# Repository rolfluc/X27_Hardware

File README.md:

# X27_Hardware
Repo to house the Hardware file for the x27 Dial Motor

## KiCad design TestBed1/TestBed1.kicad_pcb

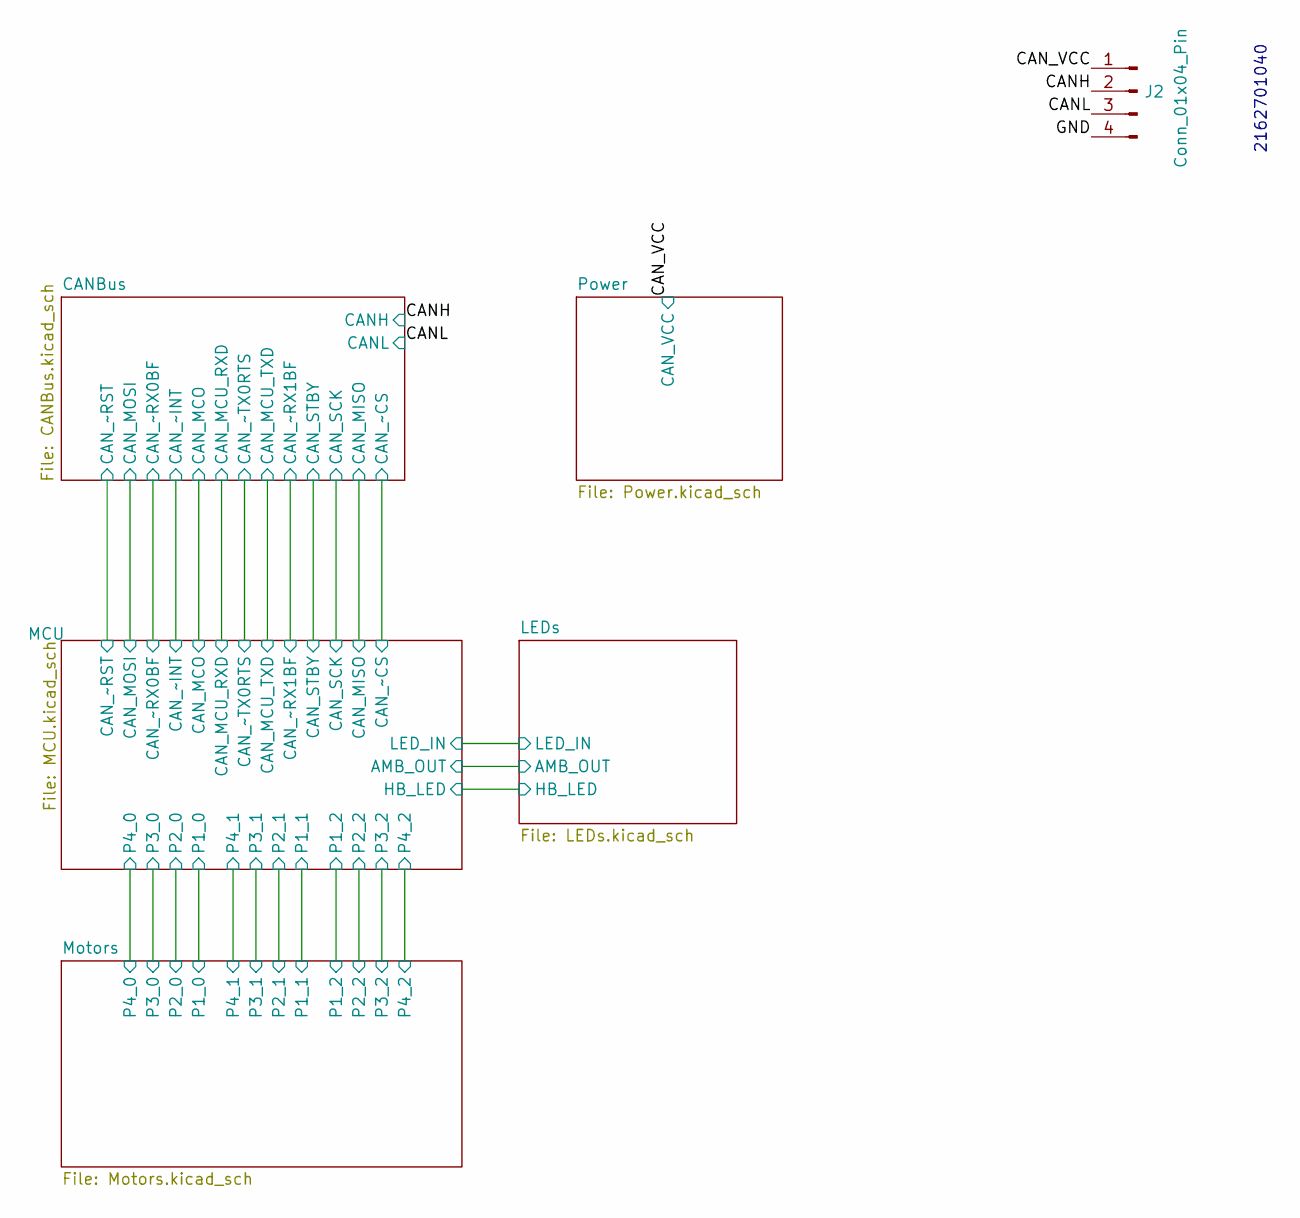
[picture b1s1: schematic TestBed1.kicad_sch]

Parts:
J2: Conn_01x04_Pin; CONN_70551-xxxx_04_MOL

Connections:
/CANH: J2.2; also elsewhere on the board
/CANL: J2.3; also elsewhere on the board
/CAN_VCC: J2.1; also elsewhere on the board
/GND: J2.4

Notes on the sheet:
2162701040

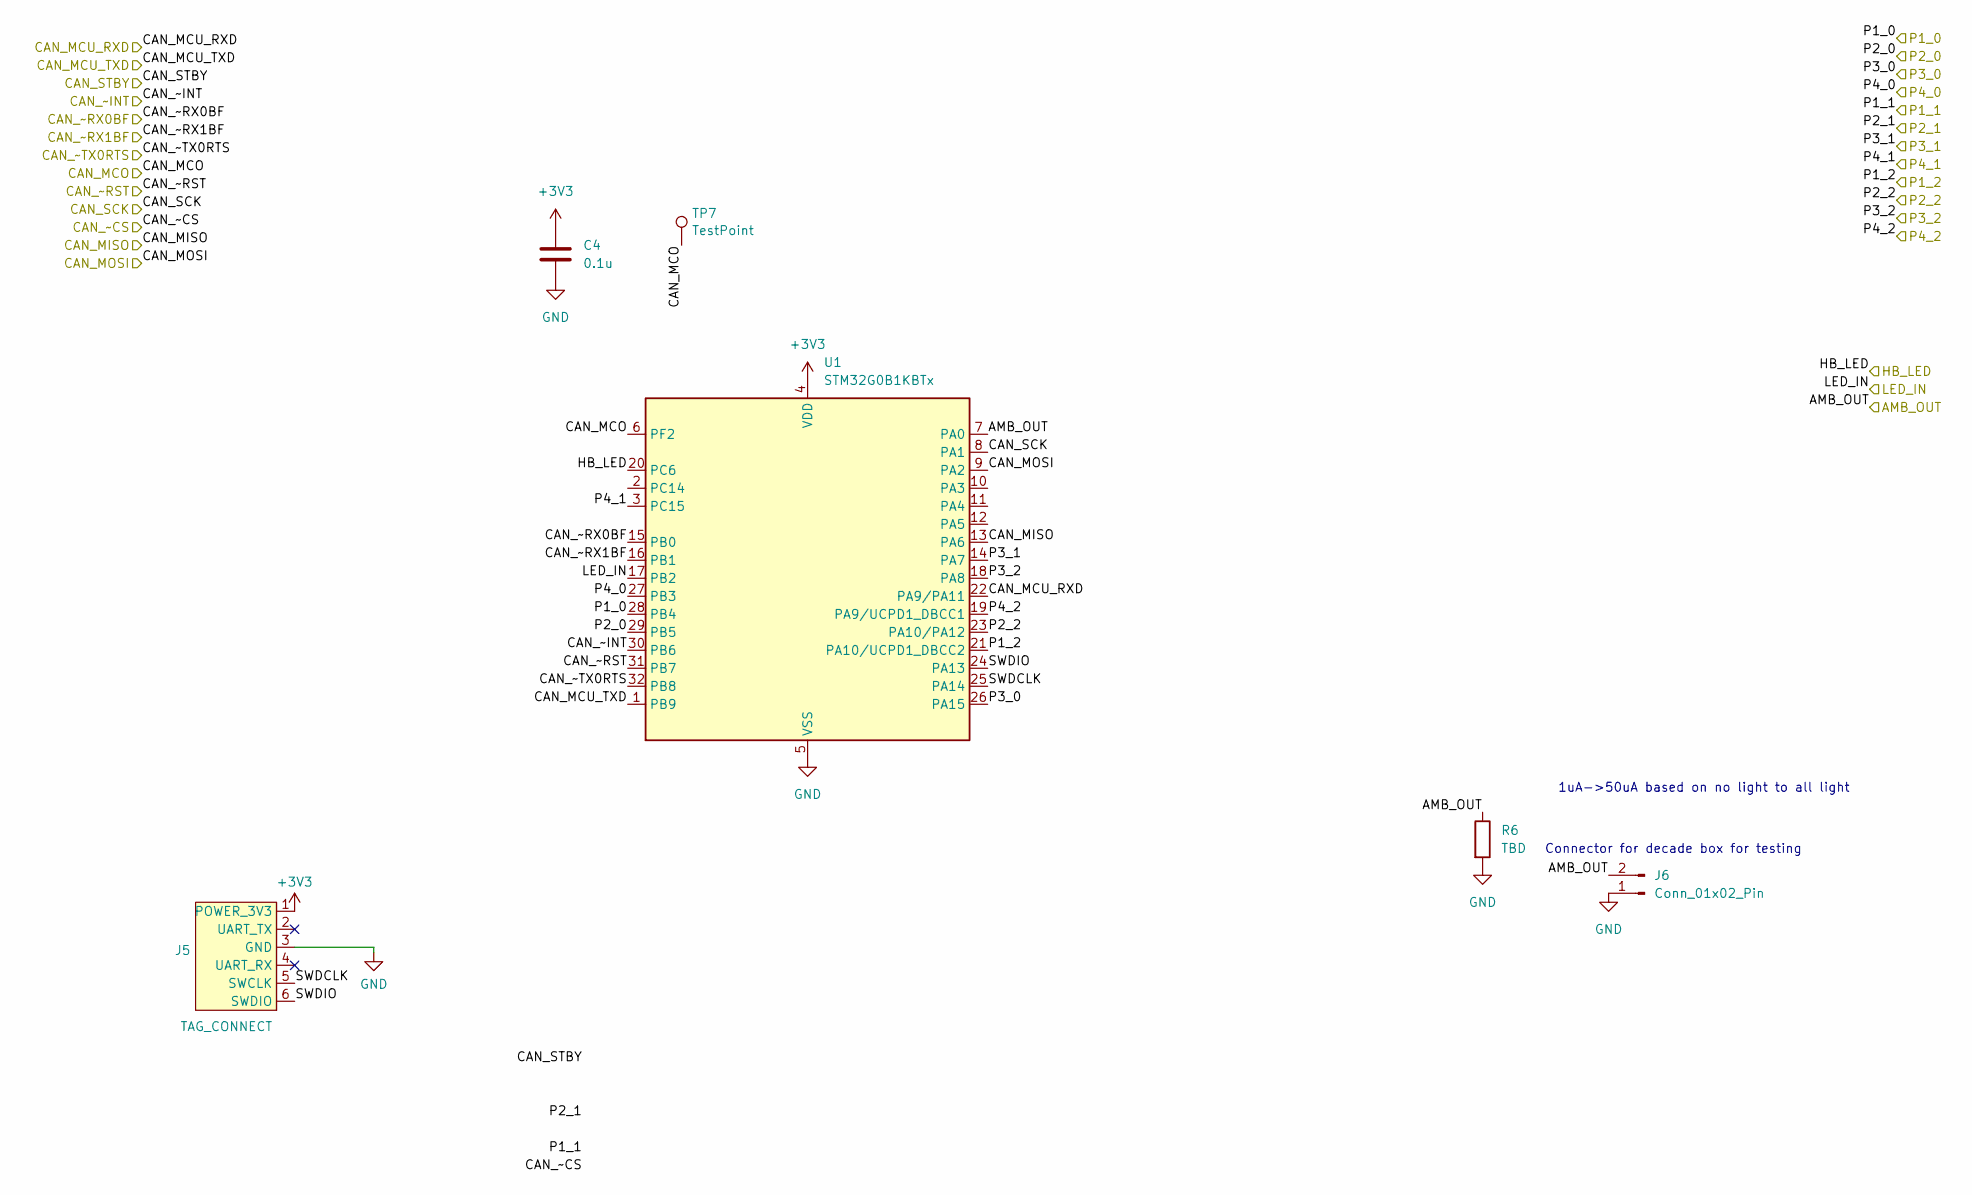
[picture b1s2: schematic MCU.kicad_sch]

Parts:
C4: 0.1u; C_0402_1005Metric_Pad0.74x0.62mm_HandSolder
J5: TAG_CONNECT; Tag-Connect_TC2030-IDC-FP_2x03_P1.27mm_Vertical
J6: Conn_01x02_Pin; PinHeader_1x02_P1.27mm_Vertical
R6: TBD; R_0402_1005Metric
TP7: TestPoint; TestPoint_Pad_1.0x1.0mm
U1: STM32G0B1KBTx; LQFP-32_7x7mm_P0.8mm

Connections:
+3V3: C4.1, J5.1 (POWER_3V3), U1.4 (VDD); also elsewhere on the board
/CANBus/CAN_MCO: TP7.1, U1.6 (PF2); also elsewhere on the board
/CANBus/CAN_MCU_RXD: U1.22 (PA9/PA11); also elsewhere on the board
/CANBus/CAN_MCU_TXD: U1.1 (PB9); also elsewhere on the board
/CANBus/CAN_MISO: U1.13 (PA6); also elsewhere on the board
/CANBus/CAN_MOSI: U1.9 (PA2); also elsewhere on the board
/CANBus/CAN_SCK: U1.8 (PA1); also elsewhere on the board
/CANBus/CAN_~INT: U1.30 (PB6); also elsewhere on the board
/CANBus/CAN_~RST: U1.31 (PB7); also elsewhere on the board
/CANBus/CAN_~RX0BF: U1.15 (PB0); also elsewhere on the board
/CANBus/CAN_~RX1BF: U1.16 (PB1); also elsewhere on the board
/CANBus/CAN_~TX0RTS: U1.32 (PB8); also elsewhere on the board
/LEDs/AMB_OUT: J6.2, R6.1, U1.7 (PA0); also elsewhere on the board
/LEDs/HB_LED: U1.20 (PC6); also elsewhere on the board
/LEDs/LED_IN: U1.17 (PB2); also elsewhere on the board
/MCU/P1_0: U1.28 (PB4); also elsewhere on the board
/MCU/P1_2: U1.21 (PA10/UCPD1_DBCC2); also elsewhere on the board
/MCU/P2_0: U1.29 (PB5); also elsewhere on the board
/MCU/P2_2: U1.23 (PA10/PA12); also elsewhere on the board
/MCU/P3_0: U1.26 (PA15); also elsewhere on the board
/MCU/P3_1: U1.14 (PA7); also elsewhere on the board
/MCU/P3_2: U1.18 (PA8); also elsewhere on the board
/MCU/P4_0: U1.27 (PB3); also elsewhere on the board
/MCU/P4_1: U1.3 (PC15); also elsewhere on the board
/MCU/P4_2: U1.19 (PA9/UCPD1_DBCC1); also elsewhere on the board
/MCU/SWDCLK: J5.5 (SWCLK), U1.25 (PA14)
/MCU/SWDIO: J5.6 (SWDIO), U1.24 (PA13)
GND: C4.2, J5.3 (GND), J6.1, R6.2, U1.5 (VSS); also elsewhere on the board

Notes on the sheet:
1uA->50uA based on no light to all light
Connector for decade box for testing

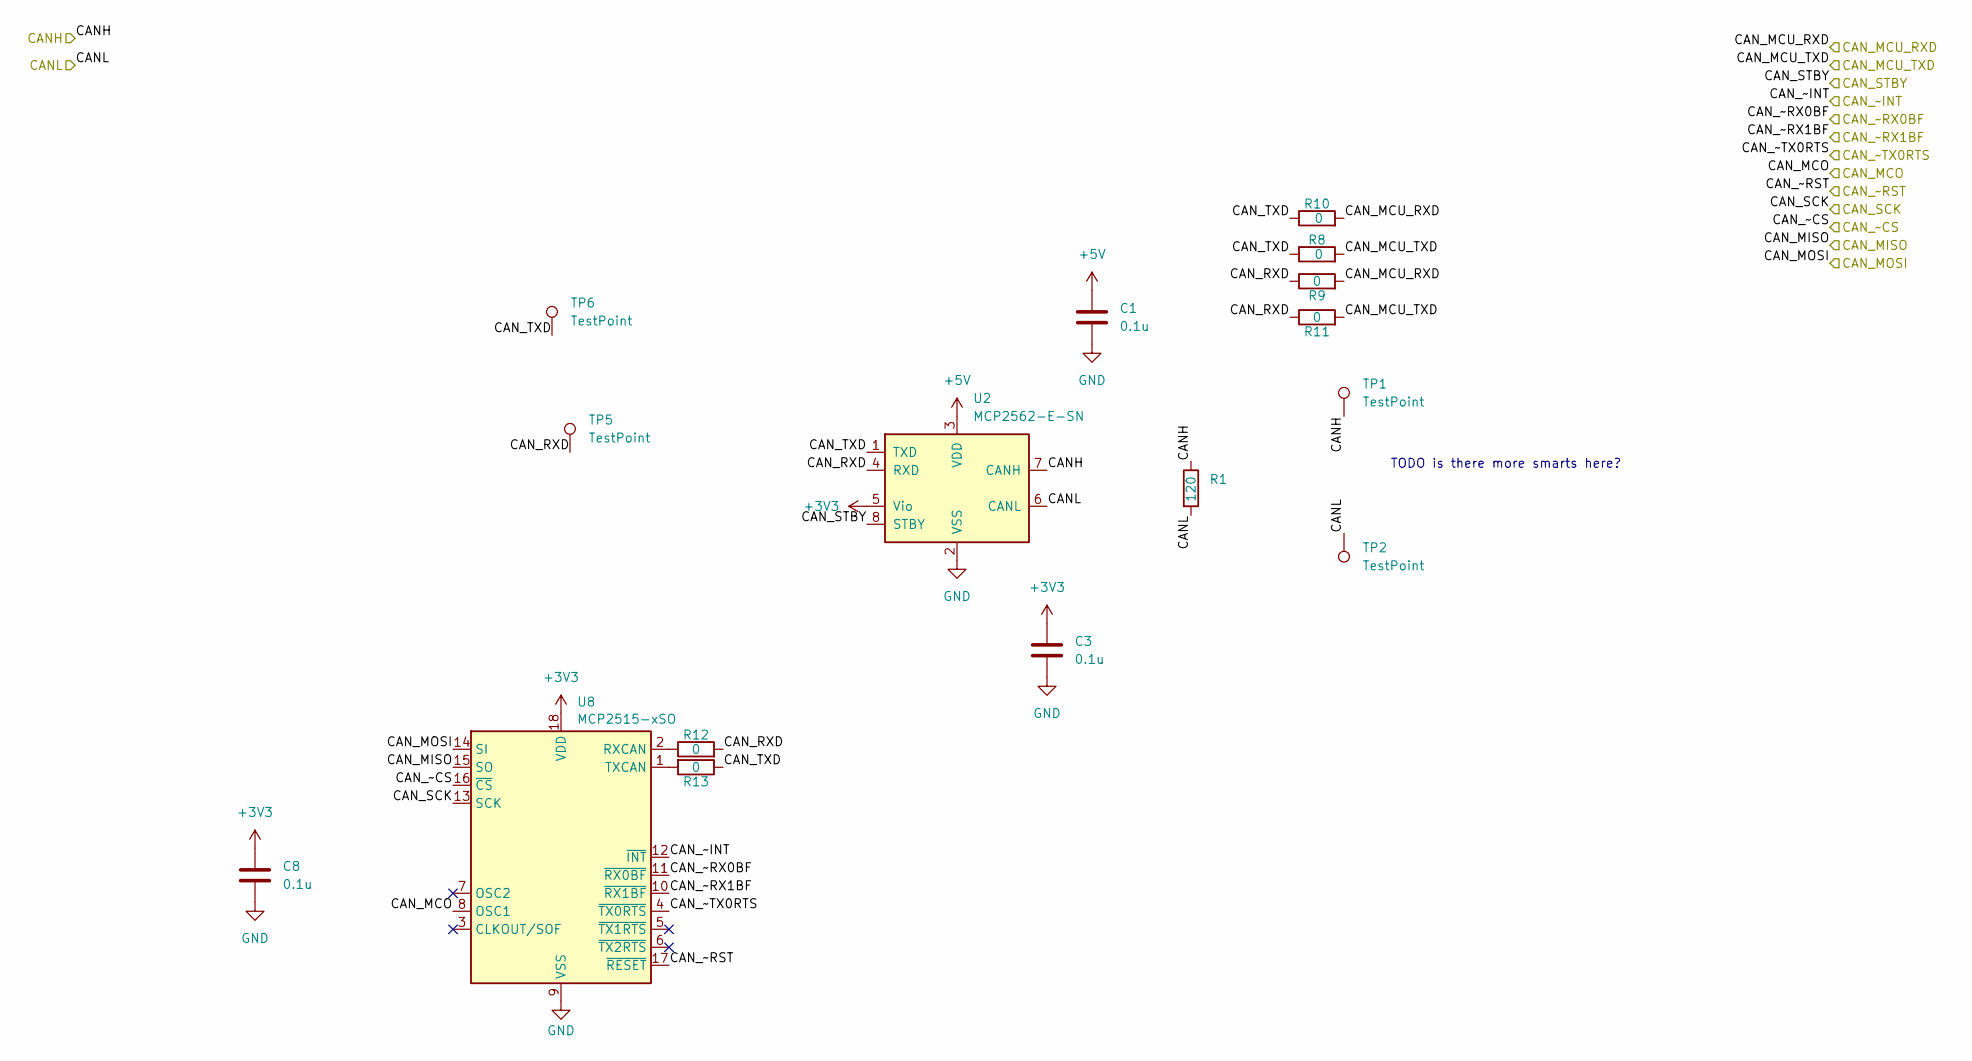
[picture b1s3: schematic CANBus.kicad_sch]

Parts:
C1, C3, C8: 0.1u; C_0402_1005Metric_Pad0.74x0.62mm_HandSolder
R1: 120; R_0805_2012Metric
R8, R9, R10, R11, R12, R13: 0; R_0402_1005Metric
TP1, TP2, TP5, TP6: TestPoint; TestPoint_Pad_1.0x1.0mm
U2: MCP2562-E-SN; SOIC-8_3.9x4.9mm_P1.27mm
U8: MCP2515-xSO; SOIC-18W_7.5x11.6mm_P1.27mm

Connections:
+3V3: C3.1, C8.1, U2.5 (Vio), U8.18 (VDD); also elsewhere on the board
+5V: C1.1, U2.3 (VDD); also elsewhere on the board
/CANBus/CAN_MCO: U8.8 (OSC1); also elsewhere on the board
/CANBus/CAN_MCU_RXD: R9.2, R10.2; also elsewhere on the board
/CANBus/CAN_MCU_TXD: R8.2, R11.2; also elsewhere on the board
/CANBus/CAN_MISO: U8.15 (SO); also elsewhere on the board
/CANBus/CAN_MOSI: U8.14 (SI); also elsewhere on the board
/CANBus/CAN_RXD: R9.1, R11.1, R12.2, TP5.1, U2.4 (RXD)
/CANBus/CAN_SCK: U8.13 (SCK); also elsewhere on the board
/CANBus/CAN_STBY: U2.8 (STBY)
/CANBus/CAN_TXD: R8.1, R10.1, R13.1, TP6.1, U2.1 (TXD)
/CANBus/CAN_~CS: U8.16 (~CS)
/CANBus/CAN_~INT: U8.12 (~INT); also elsewhere on the board
/CANBus/CAN_~RST: U8.17 (~RESET); also elsewhere on the board
/CANBus/CAN_~RX0BF: U8.11 (~RX0BF); also elsewhere on the board
/CANBus/CAN_~RX1BF: U8.10 (~RX1BF); also elsewhere on the board
/CANBus/CAN_~TX0RTS: U8.4 (~TX0RTS); also elsewhere on the board
/CANH: R1.1, TP1.1, U2.7 (CANH); also elsewhere on the board
/CANL: R1.2, TP2.1, U2.6 (CANL); also elsewhere on the board
GND: C1.2, C3.2, C8.2, U2.2 (VSS), U8.9 (VSS); also elsewhere on the board
unnamed: R12.1, U8.2 (RXCAN)
unnamed: R13.2, U8.1 (TXCAN)

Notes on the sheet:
TODO is there more smarts here?

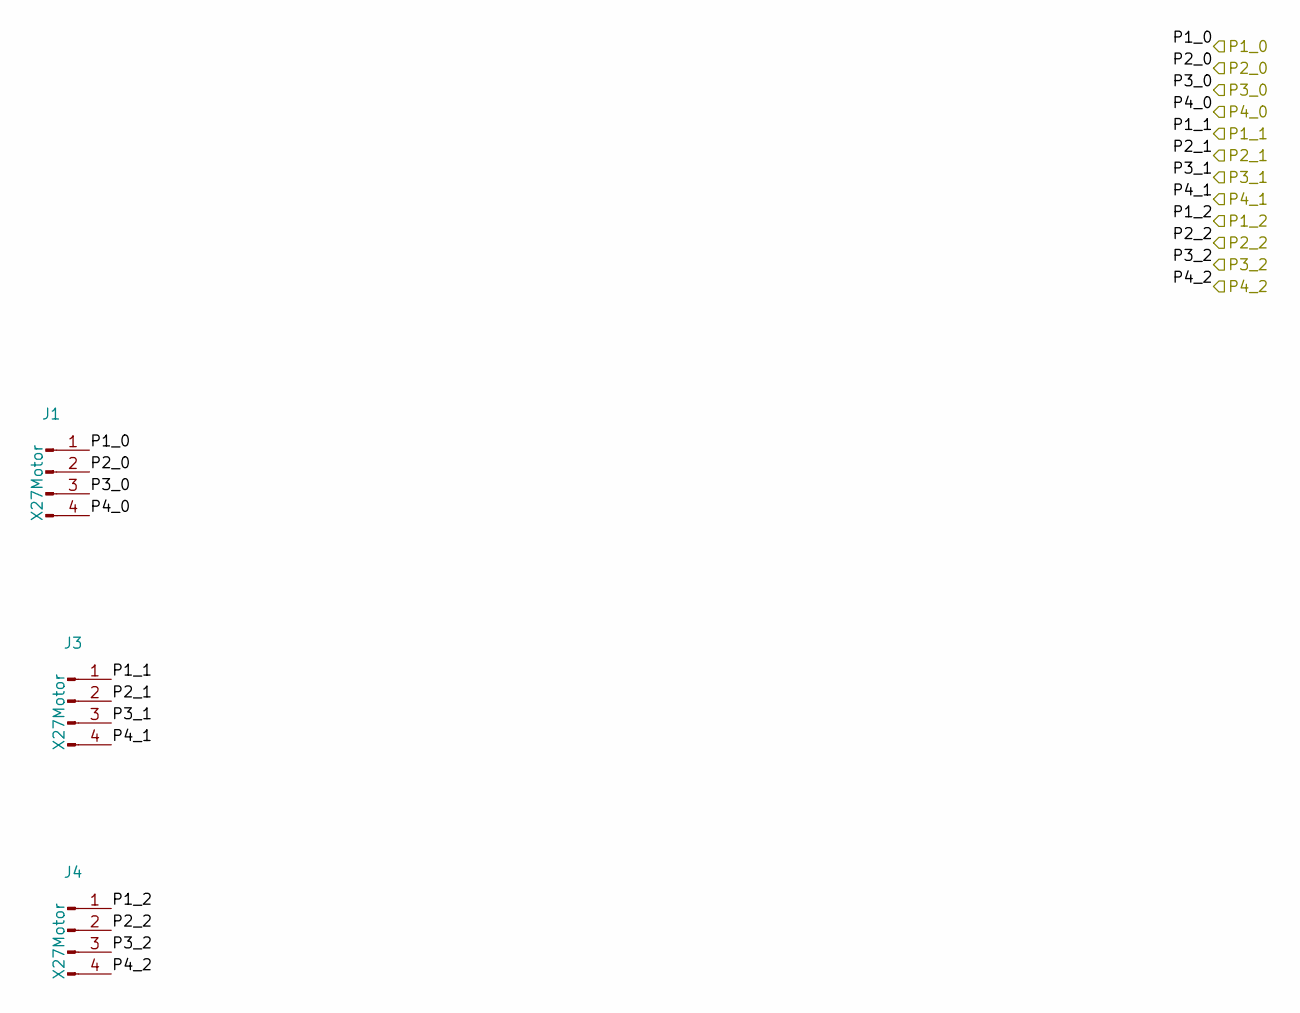
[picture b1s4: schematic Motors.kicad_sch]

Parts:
J1, J3, J4: X27Motor; X27-168

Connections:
/MCU/P1_0: J1.1; also elsewhere on the board
/MCU/P1_1: J3.1
/MCU/P1_2: J4.1; also elsewhere on the board
/MCU/P2_0: J1.2; also elsewhere on the board
/MCU/P2_1: J3.2
/MCU/P2_2: J4.2; also elsewhere on the board
/MCU/P3_0: J1.3; also elsewhere on the board
/MCU/P3_1: J3.3; also elsewhere on the board
/MCU/P3_2: J4.3; also elsewhere on the board
/MCU/P4_0: J1.4; also elsewhere on the board
/MCU/P4_1: J3.4; also elsewhere on the board
/MCU/P4_2: J4.4; also elsewhere on the board

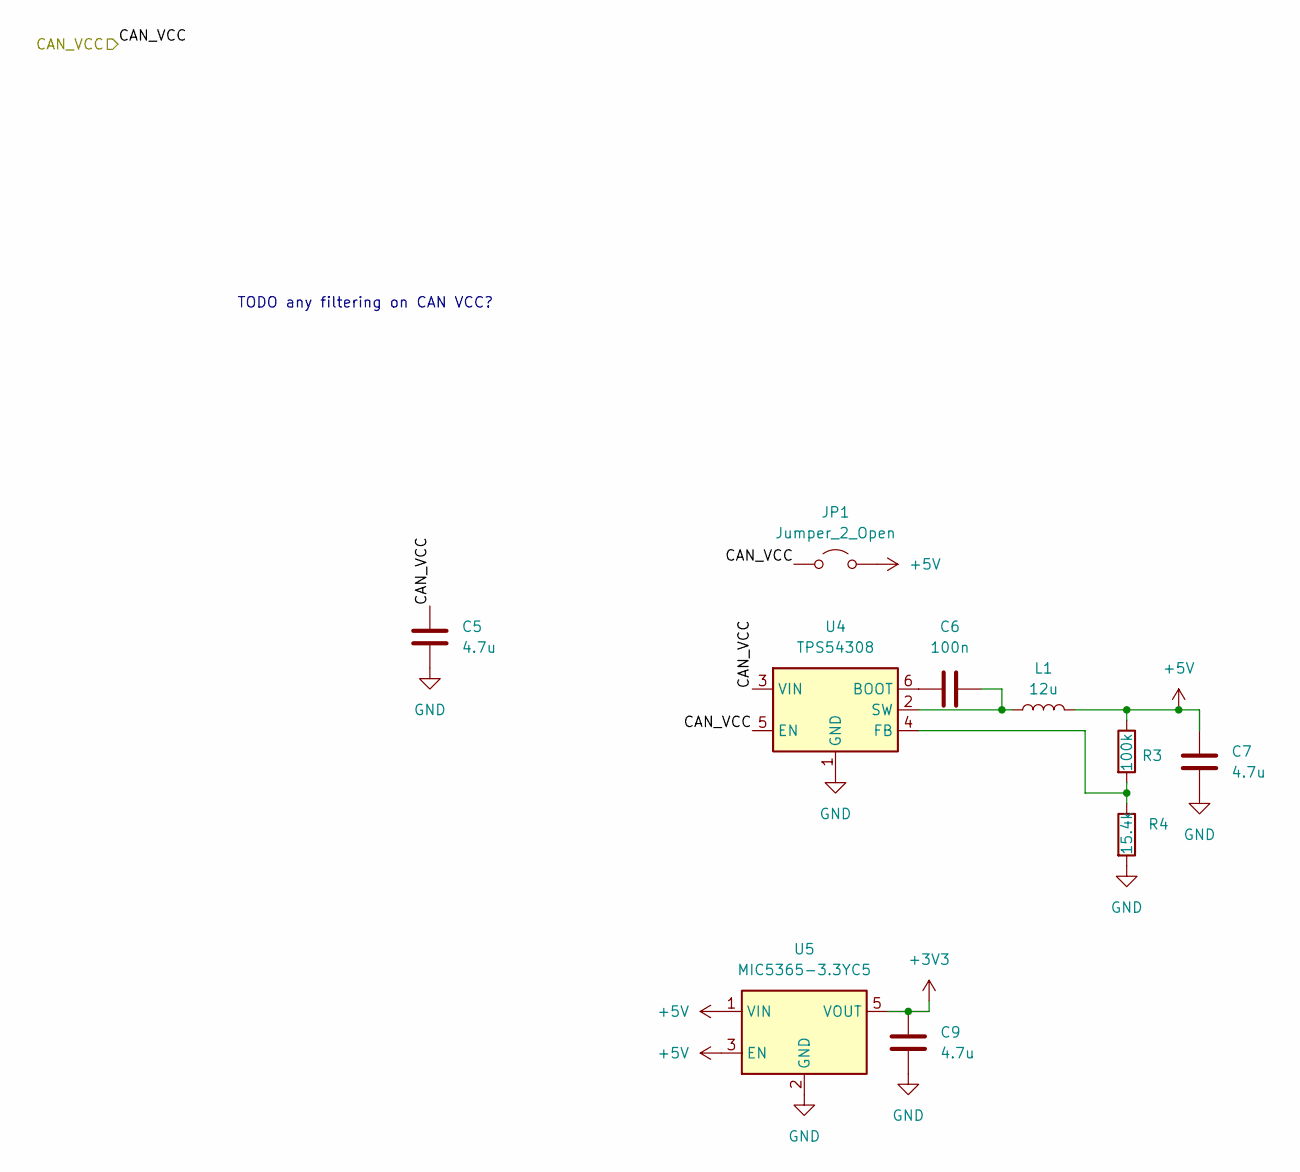
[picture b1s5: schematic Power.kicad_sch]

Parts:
C5: 4.7u; C_0805_2012Metric
C6: 100n; C_0603_1608Metric
C7, C9: 4.7u; C_0603_1608Metric
JP1: Jumper_2_Open; R_0805_2012Metric
L1: 12u; L_1812_4532Metric
R3: 100k; R_0402_1005Metric
R4: 15.4k; R_0402_1005Metric
U4: TPS54308; SOT-23-6
U5: MIC5365-3.3YC5; SOT-353_SC-70-5

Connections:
+3V3: C9.1, U5.5 (VOUT); also elsewhere on the board
+5V: C7.1, JP1.2 (B), L1.2, R3.1, U5.1 (VIN), U5.3 (EN); also elsewhere on the board
/CAN_VCC: C5.1, JP1.1 (A), U4.3 (VIN), U4.5 (EN); also elsewhere on the board
GND: C5.2, C7.2, C9.2, R4.2, U4.1 (GND), U5.2 (GND); also elsewhere on the board
unnamed: C6.1, U4.6 (BOOT)
unnamed: R3.2, R4.1, U4.4 (FB)
unnamed: C6.2, L1.1, U4.2 (SW)

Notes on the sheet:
TODO any filtering on CAN VCC?

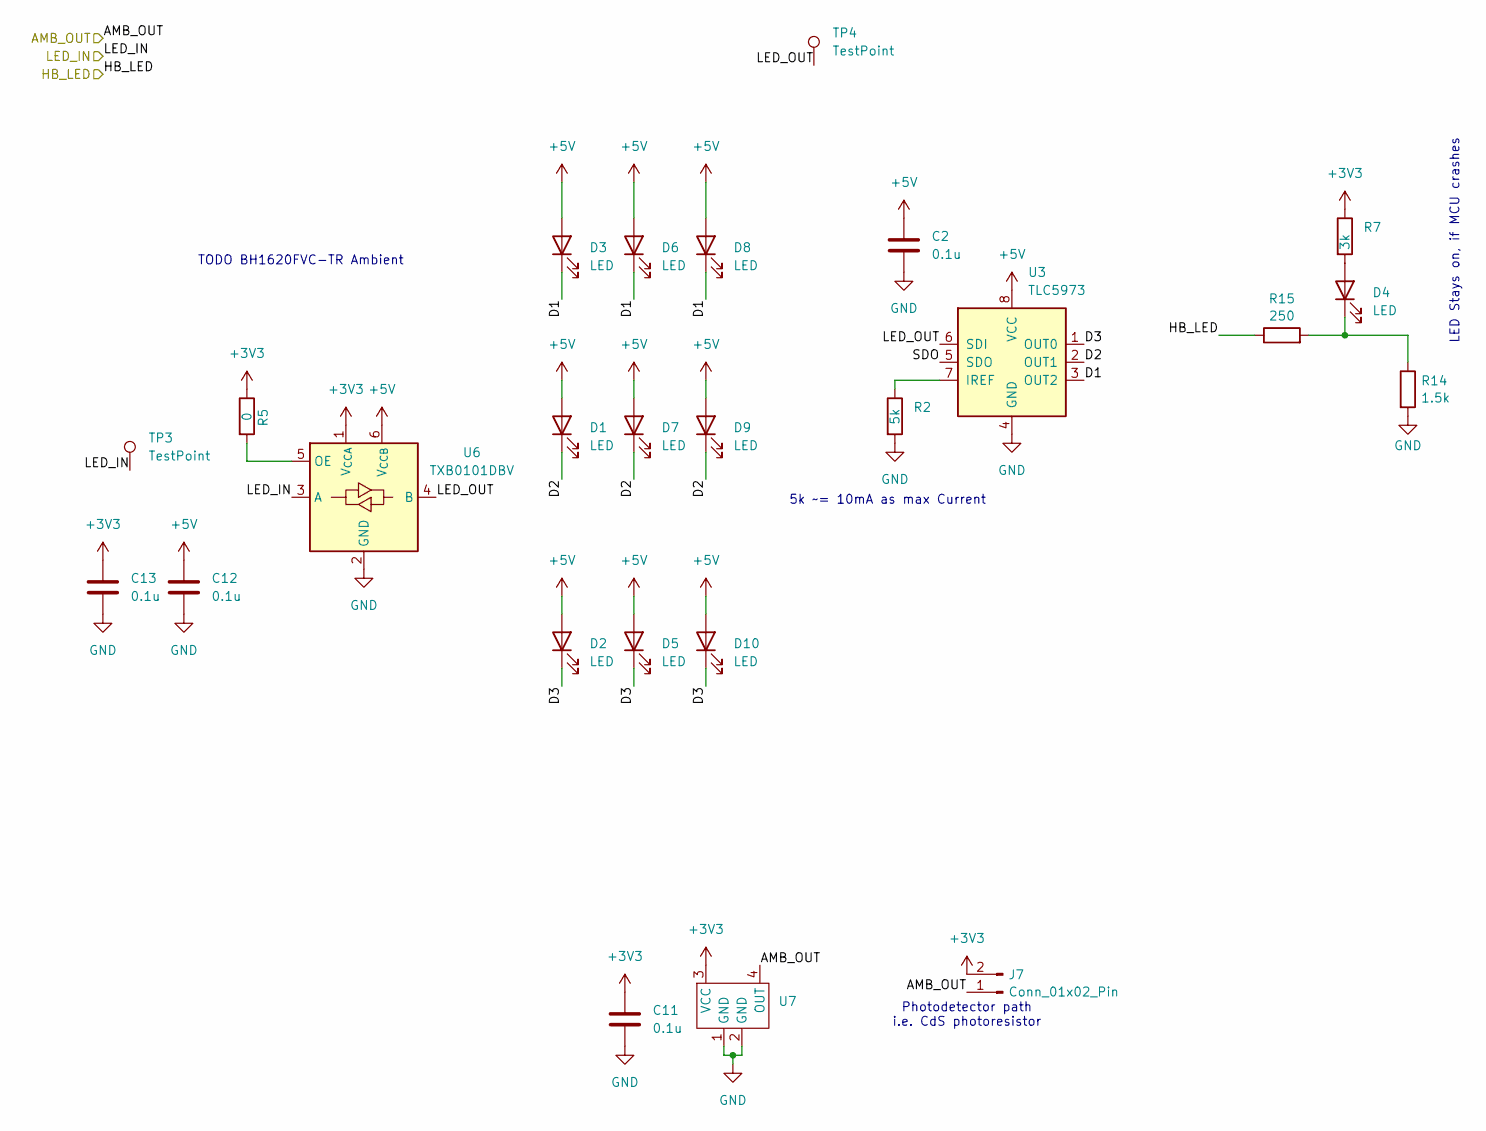
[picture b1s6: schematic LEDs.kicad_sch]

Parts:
C2, C11, C12, C13: 0.1u; C_0402_1005Metric_Pad0.74x0.62mm_HandSolder
D1, D2, D3, D5, D6, D7, D8, D9, D10: LED; LED_Luminus_MP-3030-1100_3.0x3.0mm
D4: LED; LED_0603_1608Metric
J7: Conn_01x02_Pin; PinHeader_1x02_P1.27mm_Vertical
R2: 5k; R_0402_1005Metric
R5: 0; R_0402_1005Metric
R7: 3k; R_0603_1608Metric
R14: 1.5k; R_0402_1005Metric
R15: 250; R_0402_1005Metric
TP3, TP4: TestPoint; TestPoint_Pad_1.0x1.0mm
U3: TLC5973; SOIC-8_3.9x4.9mm_P1.27mm
U6: TXB0101DBV; SOT-23-6
U7: SFH_5711-23-Z

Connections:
+3V3: C11.1, C13.1, J7.2, R5.1, R7.1, U6.1 (V_{CCA}), U7.3 (VCC); also elsewhere on the board
+5V: C2.1, C12.1, D1.2 (A), D2.2 (A), D3.2 (A), D5.2 (A), D6.2 (A), D7.2 (A), D8.2 (A), D9.2 (A), D10.2 (A), U3.8 (VCC), U6.6 (V_{CCB}); also elsewhere on the board
/LEDs/AMB_OUT: J7.1, U7.4 (OUT); also elsewhere on the board
/LEDs/D1: D3.1 (K), D6.1 (K), D8.1 (K), U3.3 (OUT2)
/LEDs/D2: D1.1 (K), D7.1 (K), D9.1 (K), U3.2 (OUT1)
/LEDs/D3: D2.1 (K), D5.1 (K), D10.1 (K), U3.1 (OUT0)
/LEDs/HB_LED: R15.1; also elsewhere on the board
/LEDs/LED_IN: TP3.1, U6.3 (A); also elsewhere on the board
/LEDs/LED_OUT: TP4.1, U3.6 (SDI), U6.4 (B)
/LEDs/SDO: U3.5 (SDO)
GND: C2.2, C11.2, C12.2, C13.2, R2.2, R14.2, U3.4 (GND), U6.2 (GND), U7.1 (GND), U7.2 (GND); also elsewhere on the board
unnamed: D4.2 (A), R7.2
unnamed: D4.1 (K), R14.1, R15.2
unnamed: R2.1, U3.7 (IREF)
unnamed: R5.2, U6.5 (OE)

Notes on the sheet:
TODO BH1620FVC-TR Ambient
LED Stays on, if MCU crashes
Photodetector path i.e. CdS photoresistor
5k ~= 10mA as max Current

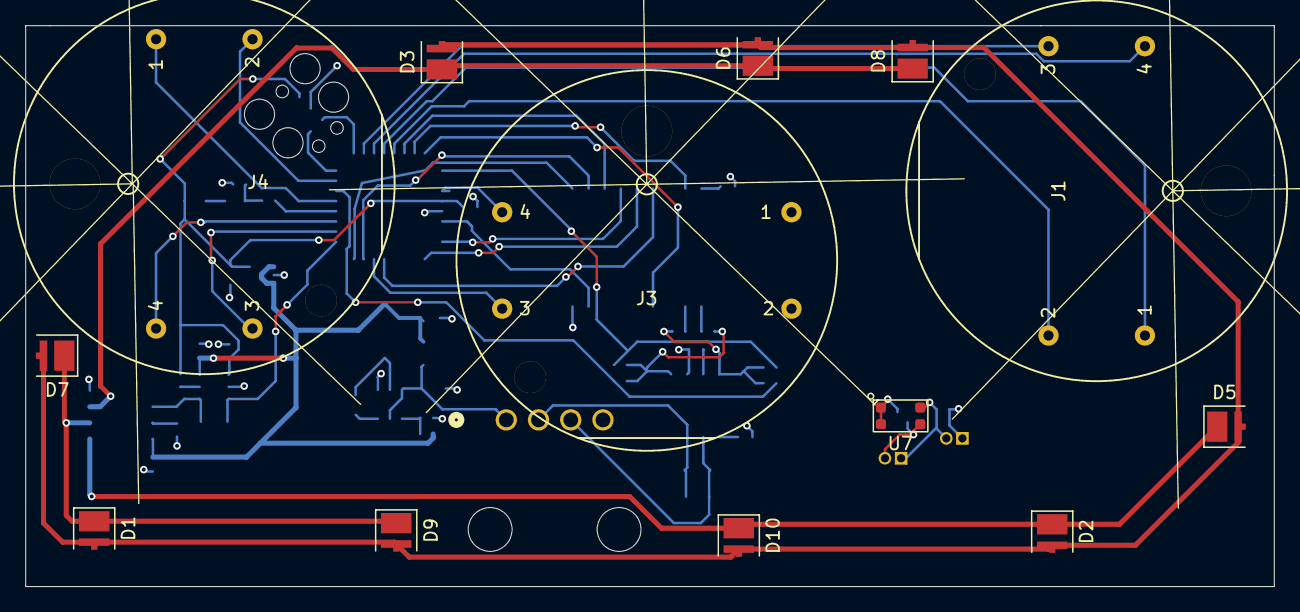
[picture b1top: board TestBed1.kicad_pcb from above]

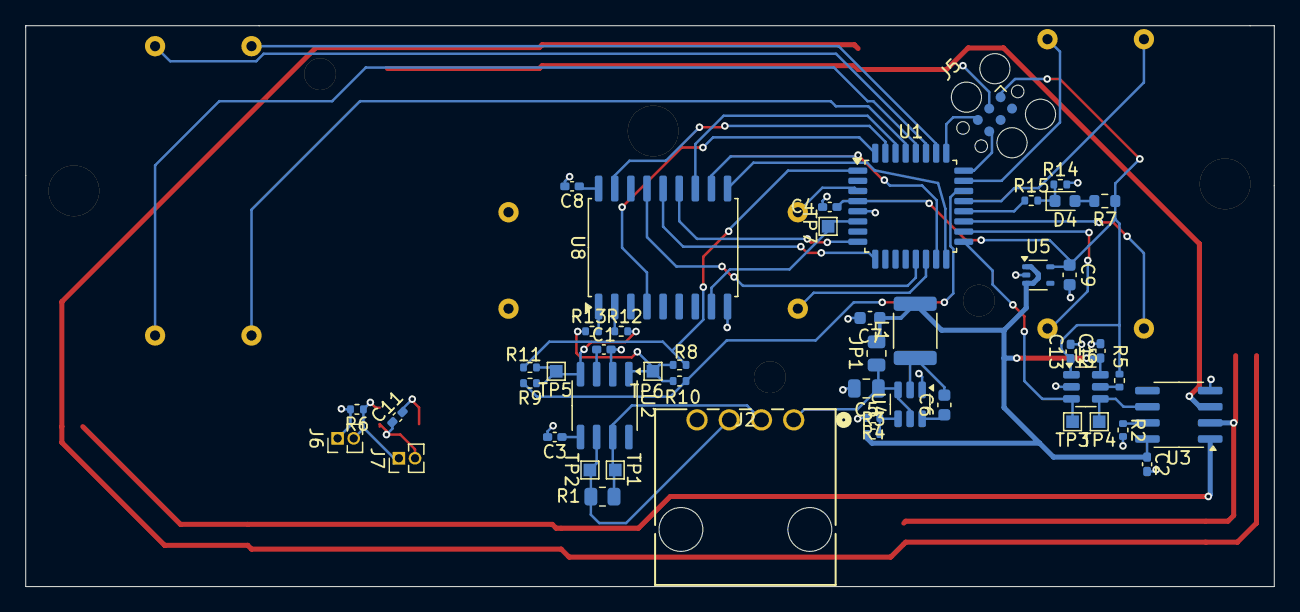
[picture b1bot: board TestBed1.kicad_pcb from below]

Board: 2 copper layers, 98.4 x 44.2 mm, 61 parts (48 on the bottom side), 47 nets.

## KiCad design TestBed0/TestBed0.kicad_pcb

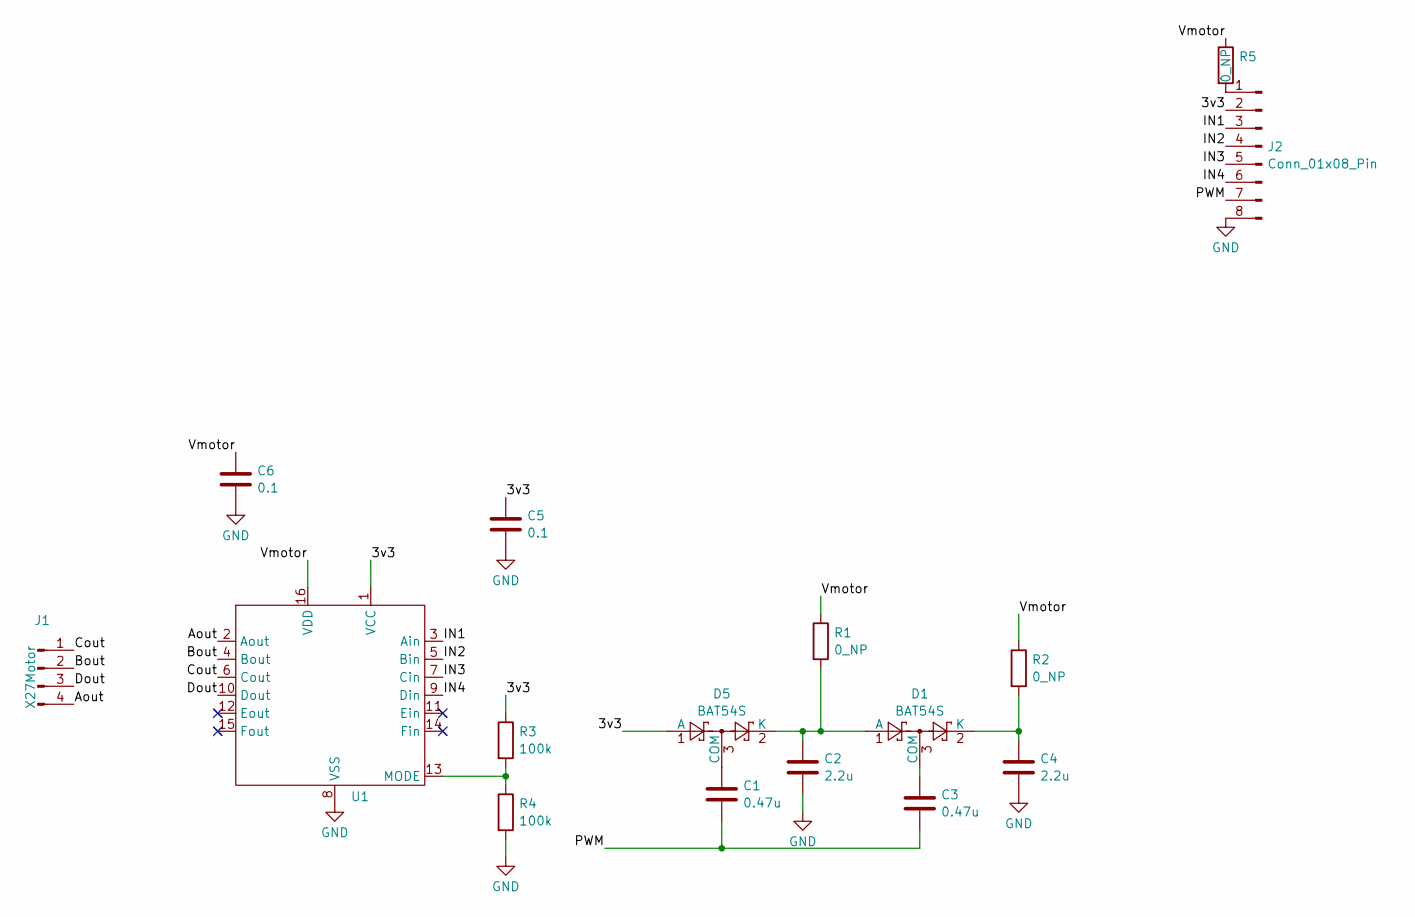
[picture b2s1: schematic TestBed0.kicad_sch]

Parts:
C1, C3: 0.47u; C_0402_1005Metric_Pad0.74x0.62mm_HandSolder
C2, C4: 2.2u; C_0402_1005Metric_Pad0.74x0.62mm_HandSolder
C5, C6: 0.1; C_0402_1005Metric_Pad0.74x0.62mm_HandSolder
D1, D5: BAT54S; SOT-23
J1: X27Motor; X27-168
J2: Conn_01x08_Pin; PinHeader_1x08_P2.54mm_Vertical
R1, R2, R5: 0_NP; R_0402_1005Metric
R3, R4: 100k; R_0402_1005Metric
U1: TSSOP-16_4.4x5mm_P0.65mm

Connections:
/3v3: C5.1, D5.1 (A), J2.2, R3.1, U1.1 (VCC)
/Aout: J1.4, U1.2 (Aout)
/Bout: J1.2, U1.4 (Bout)
/Cout: J1.1, U1.6 (Cout)
/Dout: J1.3, U1.10 (Dout)
/IN1: J2.3, U1.3 (Ain)
/IN2: J2.4, U1.5 (Bin)
/IN3: J2.5, U1.7 (Cin)
/IN4: J2.6, U1.9 (Din)
/PWM: C1.1, C3.1, J2.7
/Vmotor: C6.1, R1.1, R2.1, R5.1, U1.16 (VDD)
GND: C2.2, C4.2, C5.2, C6.2, J2.8, R4.2, U1.8 (VSS)
unnamed: C2.1, D1.1 (A), D5.2 (K), R1.2
unnamed: C3.2, D1.3 (COM)
unnamed: C4.1, D1.2 (K), R2.2
unnamed: C1.2, D5.3 (COM)
unnamed: J2.1, R5.2
unnamed: R3.2, R4.1, U1.13 (MODE)

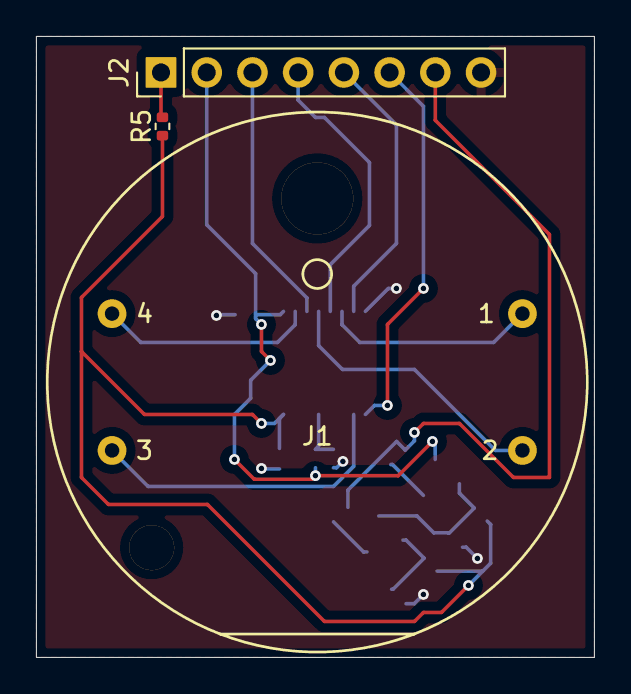
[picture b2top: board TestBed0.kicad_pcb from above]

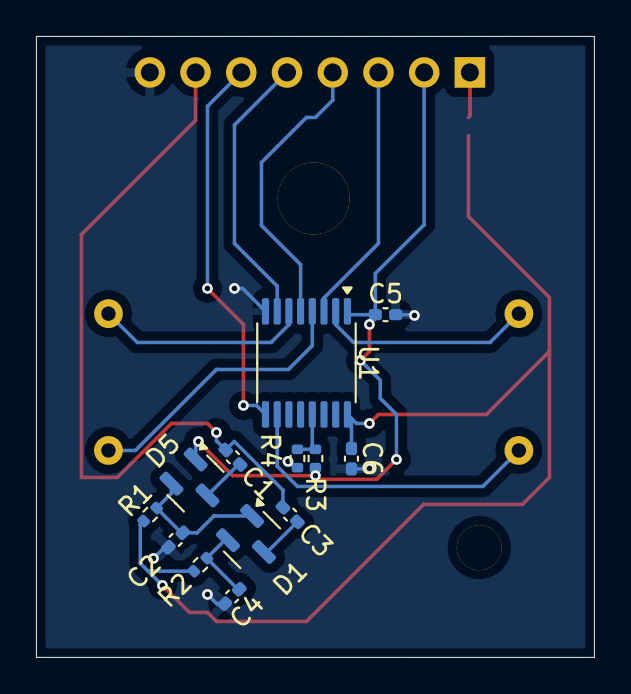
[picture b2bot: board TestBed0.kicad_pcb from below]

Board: 2 copper layers, 31.0 x 34.5 mm, 16 parts (13 on the bottom side), 18 nets.

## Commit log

2025-03-05 Adding base Motor PCB
2025-03-05 Adding Basic README
2025-03-05 Test 1 - Dickson and Level Shifter
    Dickson Multiplier, while does work, is not reliable
    per unit, i.e. if there is ANY resistance it cannot keep up.
    Level Shifter might also technically be the problem but cannot confirm
2025-03-17 Initial Checkin
2025-03-19 WIP Adding new sheets.
2025-03-21 WIP - Parts Assigned
    Need footprints, and MCU connections, but WIP
2025-03-21 LED Update for more work
2025-03-21 Rough Grouping, Passive Footprint Assignment
2025-03-21 WIP Further Grouping
2025-03-25 Schematic Assignment, board assignemtn and rough placement
2025-03-25 WIP placement
2025-03-25 Board Outline and Connector Placement
2025-03-25 WIP need layout and reconfiguring
2025-03-27 Rough Placement and board outline
2025-03-28 WIP - routing
